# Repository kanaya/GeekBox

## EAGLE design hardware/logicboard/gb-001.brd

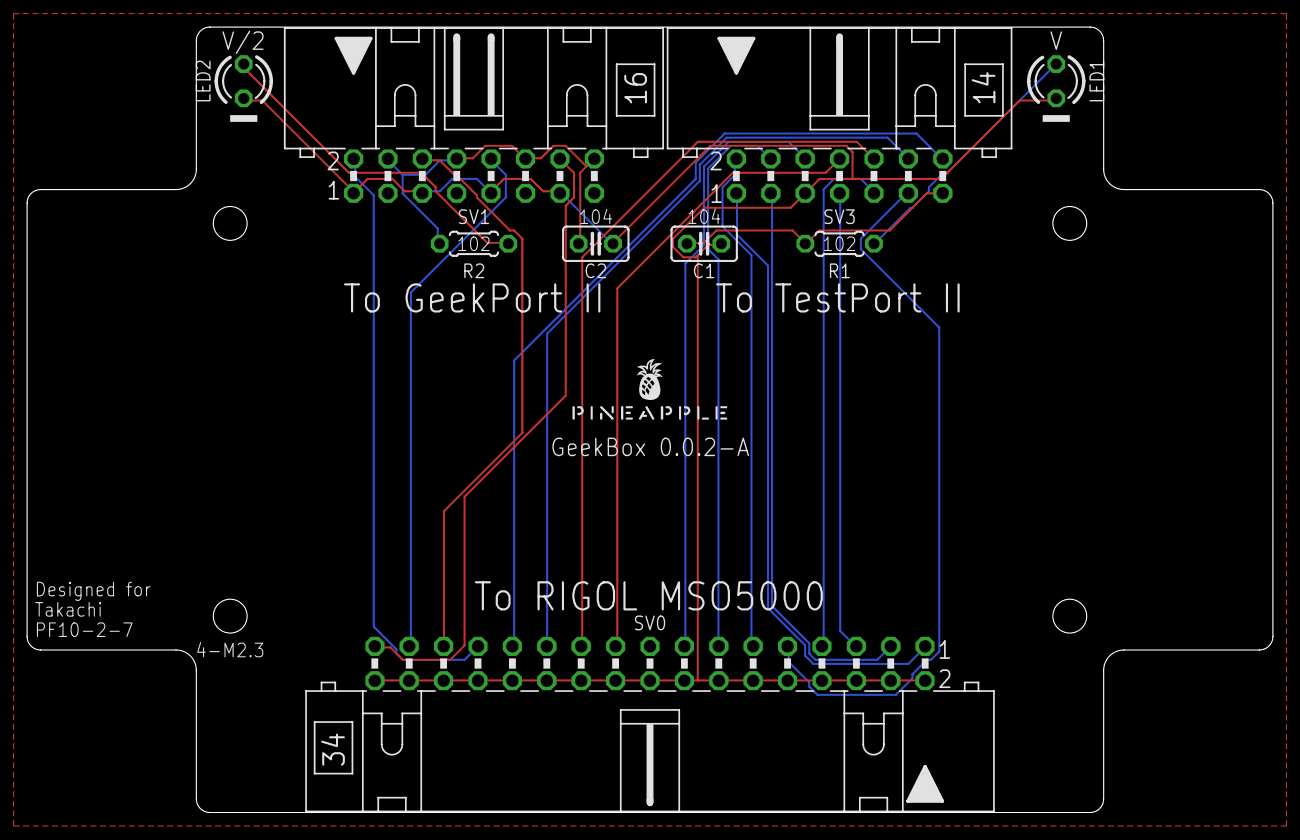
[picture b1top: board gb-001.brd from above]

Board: 2 copper layers, 92.0 x 58.0 mm, 10 parts (0 on the bottom side), 21 nets.

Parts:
C1, C2: C025-025X050
LED1, LED2: LED3MM
R1, R2: 1k; 0204/5
SV0: ML34L
SV1: ML16L
SV3: ML14L
U$1: PINEAPPLE450_SILK

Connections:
GB00: SV0.1, SV3.1
GB01: SV0.3, SV3.3
GB02: SV0.5, SV3.7
GB03: SV0.7, SV3.9
GB04: SV0.9, SV3.11
GB05: SV0.11, SV3.2
GB06: SV0.13, SV3.4
GB07: SV0.15, SV3.6
GB08: SV0.19, SV3.8
GB09: SV0.21, SV3.10
GB10: SV0.23, SV3.12
GB11: SV0.25, SV3.14
GB12: SV0.27, SV1.2
GB13: SV0.29, SV1.6
GB14: SV0.31, SV1.10
GB15: SV0.33, SV1.14
GND: C1.2, C2.2, LED1.K, LED2.K, SV0.2, SV0.4, SV0.6, SV0.8, SV0.10, SV0.12, SV0.14, SV0.16, SV0.18, SV0.20, SV0.22, SV0.24, SV0.26, SV0.28, SV0.30, SV0.32, SV0.34, SV1.1, SV1.5, SV1.9, SV1.13, SV3.5
VCC: C1.1, R1.1, SV3.13
VCC2LED: LED2.A, R2.2
VCC/2: C2.1, R2.1, SV1.4, SV1.8, SV1.12, SV1.16
VCCLED: LED1.A, R1.2

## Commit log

2022-02-02 Copied from Pineapple IId 0.0.2-B.
2022-02-02 Expanded logicboard.
2022-02-02 Re-centered logicboard.
2022-02-02 Good one.
2022-02-02 Routed.
2022-02-02 Added extra pins.
2022-02-02 Added PWR led.
2022-02-07 Added GeekPort.
2022-02-08 Added signal names and silk patterns.
2022-02-08 Redesigned for PF10-2-7.
2022-02-09 Added GND pattern.
2022-02-09 Renamed signals.
2022-02-09 Silk.
2022-02-11 Added capacitors.
2022-04-06 Changed silk.
